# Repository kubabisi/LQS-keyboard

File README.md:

# LQS keyboard
**L**ow profile **Q**uiet **S**plit keyboard

## Why have I decided to build a keyboard?
A few years ago I received an 80% mechanical keyboard as a Christmas gift. It has been my daily driver since then.
But it has two issues:
1. It is too big and chunky to travel with or take it to school.
2. It is too loud. While it is quieter than some mechanical keyboards, you can easily hear it from the other side of my flat.

Since then Youtube algorithm has introduced me into the custom keyboard rabbit hole.
I've built a simple one using 3d printed parts and handwiring. It worked, but it was thick and after a few weeks it started to slowly break apart. First random solder joints started breaking, then the case cracked.

I wanted to build a proper keyboard, but I was too lazy to do it.
Highway gave me the motivation that I needed to finally do it.

## CAD model

[this model in Onshape](https://cad.onshape.com/documents/f682215273ff2081de69d414/w/20c4360147d88d6d7c704790/e/f61e22c6f2ff044978f79a00?renderMode=0&uiState=686bf5d5abd8817fe4595698)

## Switch layout
Switch layout was inspired by two keyboards I like: ZSA Voyager and Sofle

## Schematic

## PCB

## Case
Case for this keyboard can be 3d printed. Stl files are located in [this folder](3d-models/case)

## BOM

| Part | Quantity | Cost(PLN) | Cost (USD) | Store | Link |
| --- | --- | --- | --- | --- | --- |
| Kailh Deep Sea Whale mini switches | 58 | 113.99 | 29.70 | Aliexpress | https://pl.aliexpress.com/item/1005008927866337.html |
| Pro Micro NRF52840 | 2 | 26.78 | 7.04 | Aliexpress | https://pl.aliexpress.com/item/1005006599766097.html |
| 301230 lipo battery | 2 | 45.25 | 11.70 | Allegro.pl | https://allegro.pl/oferta/akumulator-litowo-polimerowy-110mah-3-7v-phr-2-bk-301230-17500532114 |
| 1n4148 diodes | 58 | 5.55 | 1.47 | Aliexpress | https://pl.aliexpress.com/item/4000142272546.html |
| RGB common anode 5mm led | 2 | 3.99 | 1.05 | Aliexpress | https://pl.aliexpress.com/item/4000225253691.html |
| pin sockets | 52 pins - 2 rows | 7.10 | 1.87 | Aliexpress | https://pl.aliexpress.com/item/10000000838267.html |
| PCB | 5 | 41.80 | 11.60 | JLCPCB | https://jlcpcb.com/ |
| M2 6mm flat head screws | 8 | 3.62 | 0.96 | Aliexpress | https://pl.aliexpress.com/item/1005005270702287.html | 
| M2 3x3mm heat inserts | 8 | 5.6 | 1.47 | Aliexpress | https://pl.aliexpress.com/item/1005008295045821.html |
| resistors for leds | 6 | ~4 | ~1 | |  |
| keycap set | 1 | ~120 | ~35 | | |
| 3d printed case | 2 | | | | |

Total (excluding shipping): ~380 PLN / ~$105 USD

I already have keycaps and resistors. My brother has a 3d printer at home.

Total excluding parts I have, with shipping:
- $66.77 + $21.50 (JLCPCB shipping) + $0 (Aliexpress Choice free shipping) = $88.27
- 253,61zł + 77,63zł + 0zł = 331.24zł

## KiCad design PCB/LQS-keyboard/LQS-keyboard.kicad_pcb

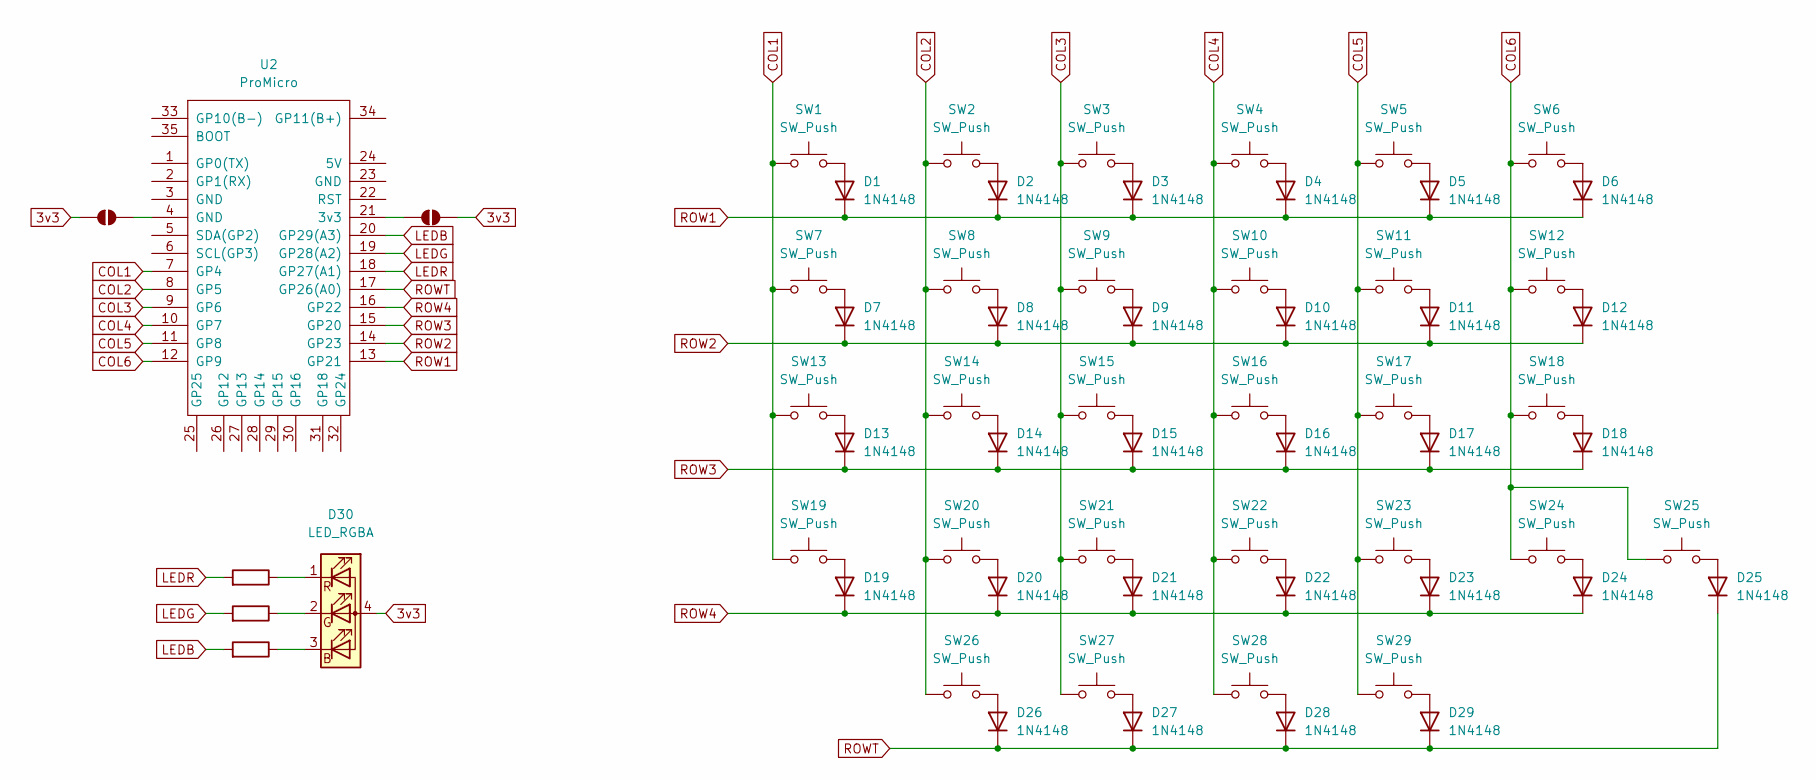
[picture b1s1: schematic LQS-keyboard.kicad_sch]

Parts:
D1, D2, D3, D4, D5, D6, D7, D8, D9, D10, D11, D12, D13, D14, D15, D16, D17, D18, D19, D20, D21, D22, D23, D24, D25, D26, D27, D28, D29: 1N4148; D_DO-35_SOD27_P7.62mm_Horizontal
D30: LED_RGBA; LED_D5.0mm-4_RGB
JP1, JP2: SolderJumper_2_Open; SolderJumper-2_P1.3mm_Open_RoundedPad1.0x1.5mm
R1, R2, R3: R; R_Axial_DIN0204_L3.6mm_D1.6mm_P7.62mm_Horizontal
SW1, SW2, SW3, SW4, SW5, SW6, SW7, SW8, SW9, SW10, SW11, SW12, SW13, SW14, SW15, SW16, SW17, SW18, SW19, SW20, SW21, SW22, SW23, SW24, SW25, SW26, SW27, SW28, SW29: SW_Push; SW_Kailh_Choc_V1V2_THT_Hybrid_doubleside
U2: ProMicro; TheOneProMicro

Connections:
3v3: D30.4 (A), JP1.2 (B), JP2.2 (B)
COL1: SW1.2, SW7.2, SW13.2, SW19.2, U2.7 (GP4)
COL2: SW2.2, SW8.2, SW14.2, SW20.2, SW26.2, U2.8 (GP5)
COL3: SW3.2, SW9.2, SW15.2, SW21.2, SW27.1, U2.9 (GP6)
COL4: SW4.2, SW10.2, SW16.2, SW22.2, SW28.1, U2.10 (GP7)
COL5: SW5.2, SW11.2, SW17.2, SW23.2, SW29.1, U2.11 (GP8)
COL6: SW6.2, SW12.2, SW18.2, SW24.2, SW25.2, U2.12 (GP9)
LEDB: R3.2, U2.20 (GP29(A3))
LEDG: R2.2, U2.19 (GP28(A2))
LEDR: R1.2, U2.18 (GP27(A1))
unnamed: D1.2 (A), SW1.1
unnamed: D2.2 (A), SW2.1
unnamed: D3.2 (A), SW3.1
unnamed: D4.2 (A), SW4.1
unnamed: D5.2 (A), SW5.1
unnamed: D6.2 (A), SW6.1
unnamed: D7.2 (A), SW7.1
unnamed: D8.2 (A), SW8.1
unnamed: D9.2 (A), SW9.1
unnamed: D10.2 (A), SW10.1
unnamed: D11.2 (A), SW11.1
unnamed: D12.2 (A), SW12.1
unnamed: D13.2 (A), SW13.1
unnamed: D14.2 (A), SW14.1
unnamed: D15.2 (A), SW15.1
unnamed: D16.2 (A), SW16.1
unnamed: D17.2 (A), SW17.1
unnamed: D18.2 (A), SW18.1
unnamed: D19.2 (A), SW19.1
unnamed: D20.2 (A), SW20.1
unnamed: D21.2 (A), SW21.1
unnamed: D22.2 (A), SW22.1
unnamed: D23.2 (A), SW23.1
unnamed: D24.2 (A), SW24.1
unnamed: D25.2 (A), SW25.1
unnamed: D26.2 (A), SW26.1
unnamed: D27.2 (A), SW27.2
unnamed: D28.2 (A), SW28.2
unnamed: D29.2 (A), SW29.2
unnamed: D30.3 (BK), R3.1
unnamed: D30.2 (GK), R2.1
unnamed: D30.1 (RK), R1.1
unnamed: JP1.1 (A), U2.4 (GND)
unnamed: JP2.1 (A), U2.21 (3v3)
ROW1: D1.1 (K), D2.1 (K), D3.1 (K), D4.1 (K), D5.1 (K), D6.1 (K), U2.13 (GP21)
ROW2: D7.1 (K), D8.1 (K), D9.1 (K), D10.1 (K), D11.1 (K), D12.1 (K), U2.14 (GP23)
ROW3: D13.1 (K), D14.1 (K), D15.1 (K), D16.1 (K), D17.1 (K), D18.1 (K), U2.15 (GP20)
ROW4: D19.1 (K), D20.1 (K), D21.1 (K), D22.1 (K), D23.1 (K), D24.1 (K), U2.16 (GP22)
ROWT: D25.1 (K), D26.1 (K), D27.1 (K), D28.1 (K), D29.1 (K), U2.17 (GP26(A0))

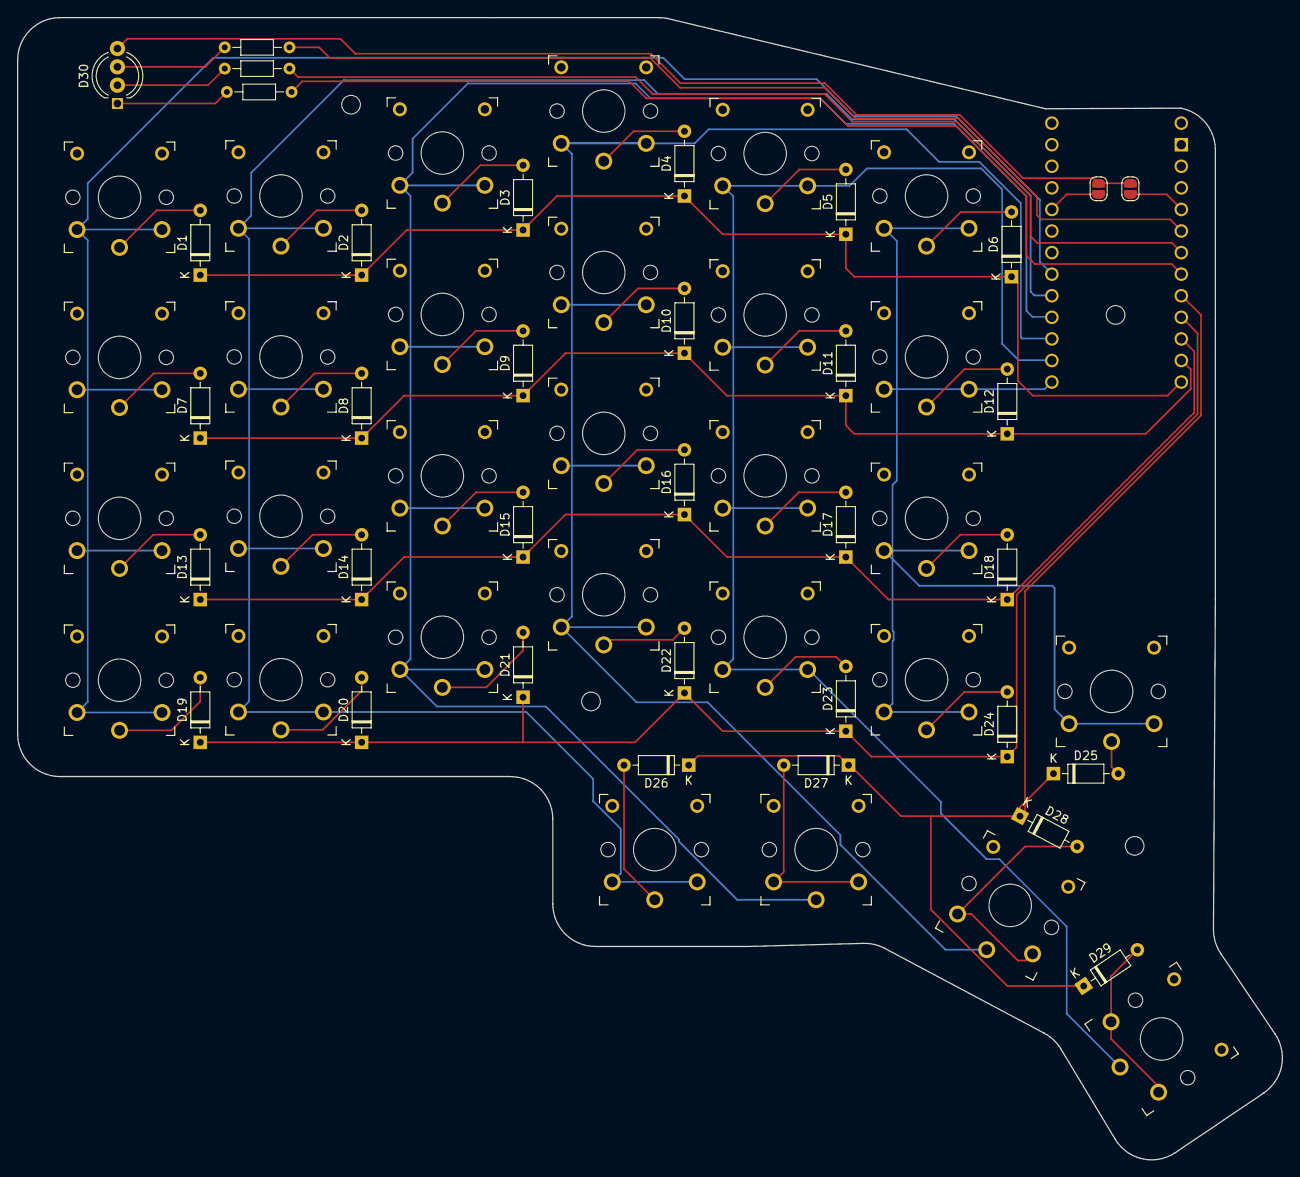
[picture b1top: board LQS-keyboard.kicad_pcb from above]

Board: 2 copper layers, 148.9 x 134.5 mm, 65 parts (0 on the bottom side), 49 nets.

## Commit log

2025-07-05 2025-07-05 update
2025-07-05 small wording update additional image
2025-07-05 update image
2025-07-06 2025-07-06 update
2025-07-07 documentation update
2025-07-07 2025-07-07 update
2025-07-07 documentation update
    add missing stl files, add total time
2025-07-07 3d model files reorganization
2025-07-07 add list of external files for kicad
2025-07-07 small BOM update
    screws need to be longer to screw through the plate
2025-07-07 change screw length in readme
2025-07-21 shells are now a bit thinner
    2mm -> 1.2mm
2025-07-22 increase led hole size
    5mm -> 5.7mm
2025-07-24 slightly increase heat insert standoffs size
2025-07-25 slightly increase gap between shell and pcb/plate
